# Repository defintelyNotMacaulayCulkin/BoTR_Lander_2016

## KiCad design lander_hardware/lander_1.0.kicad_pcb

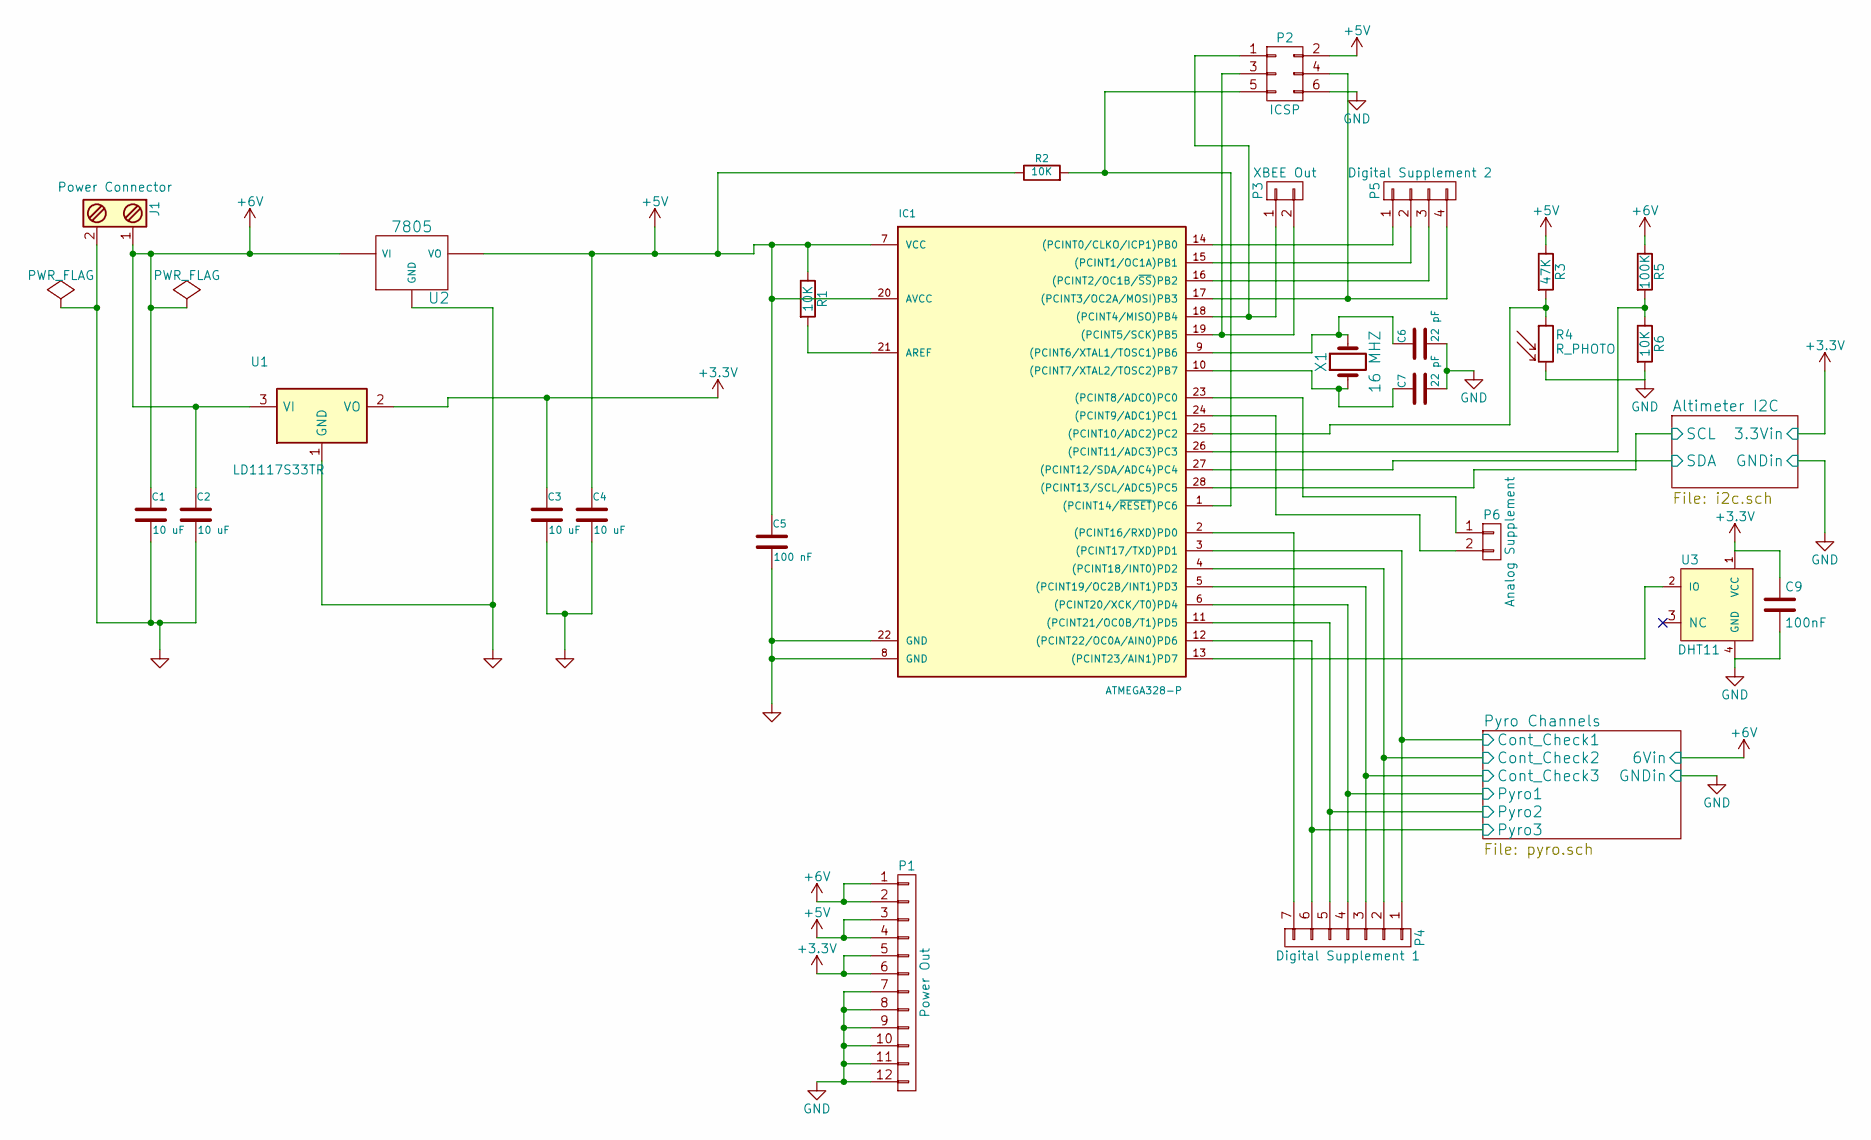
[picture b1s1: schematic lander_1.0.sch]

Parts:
C1, C2, C3, C4: 10 uF; C_Disc_D10.0mm_W2.5mm_P5.00mm
C5: 100 nF; C_Disc_D10.0mm_W2.5mm_P5.00mm
C6, C7: 22 pF; C_Disc_D10.0mm_W2.5mm_P5.00mm
C9: 100nF; C_Disc_D10.0mm_W2.5mm_P5.00mm
IC1: ATMEGA328-P; DIP-28_W7.62mm
J1: Power Connector; bornier2
P1: Power Out; Pin_Header_Straight_1x12_Pitch2.54mm
P2: ICSP; IDC_Header_Straight_6pins
P3: XBEE Out; Pin_Header_Straight_1x02_Pitch2.54mm
P4: Digital Supplement 1; Pin_Header_Straight_1x07_Pitch2.54mm
P5: Digital Supplement 2; Pin_Header_Straight_1x04_Pitch2.54mm
P6: Analog Supplement; Pin_Header_Straight_1x02_Pitch2.54mm
R1, R2, R6: 10K; R_Axial_DIN0207_L6.3mm_D2.5mm_P10.16mm_Horizontal
R3: 47K; R_Axial_DIN0207_L6.3mm_D2.5mm_P10.16mm_Horizontal
R4: R_PHOTO; Resistor_LDR_4.9x4.2_RM2.54
R5: 100K; R_Axial_DIN0207_L6.3mm_D2.5mm_P10.16mm_Horizontal
U1: LD1117S33TR; lm1117_nde
U2: 7805; TO-220
U3: DHT11; dht11
X1: 16 MHZ; Crystal_HC49-U_Vertical

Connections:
+3V3: C3.1, C9.1, P1.5, P1.6, U1.2 (VO), U3.1 (VCC); also elsewhere on the board
+5V: C4.1, C5.1, IC1.7 (VCC), IC1.20 (AVCC), P1.3, P1.4, P2.2, R1.1, R2.1, R3.1, U2.3 (VO); also elsewhere on the board
+6V: C1.1, C2.1, J1.1, P1.1, P1.2, R5.1, U1.3 (VI), U2.1 (VI); also elsewhere on the board
/Altimeter I2C/SCL: IC1.28 ((PCINT13/SCL/ADC5)PC5); also elsewhere on the board
/Altimeter I2C/SDA: IC1.27 ((PCINT12/SDA/ADC4)PC4); also elsewhere on the board
/Pyro Channels/Cont_Check1: IC1.3 ((PCINT17/TXD)PD1), P4.1; also elsewhere on the board
/Pyro Channels/Cont_Check2: IC1.4 ((PCINT18/INT0)PD2), P4.2; also elsewhere on the board
/Pyro Channels/Cont_Check3: IC1.5 ((PCINT19/OC2B/INT1)PD3), P4.3; also elsewhere on the board
/Pyro Channels/Pyro1: IC1.6 ((PCINT20/XCK/T0)PD4), P4.4; also elsewhere on the board
/Pyro Channels/Pyro2: IC1.11 ((PCINT21/OC0B/T1)PD5), P4.5; also elsewhere on the board
/Pyro Channels/Pyro3: IC1.12 ((PCINT22/OC0A/AIN0)PD6), P4.6; also elsewhere on the board
GND: C1.2, C2.2, C3.2, C4.2, C5.2, C6.2, C7.2, C9.2, IC1.8 (GND), IC1.22 (GND), J1.2, P1.7, P1.8, P1.9, P1.10, P1.11, P1.12, P2.6, R4.2, R6.2, U1.1 (GND), U2.2 (GND), U3.4 (GND); also elsewhere on the board
unnamed: C6.1, IC1.9 ((PCINT6/XTAL1/TOSC1)PB6), X1.2
unnamed: C7.1, IC1.10 ((PCINT7/XTAL2/TOSC2)PB7), X1.1
unnamed: IC1.1 ((PCINT14/~RESET~)PC6), P2.5, R2.2
unnamed: IC1.2 ((PCINT16/RXD)PD0), P4.7
unnamed 16: IC1.13 ((PCINT23/AIN1)PD7), U3.2 (IO); also elsewhere on the board
unnamed: IC1.14 ((PCINT0/CLKO/ICP1)PB0), P5.1
unnamed: IC1.15 ((PCINT1/OC1A)PB1), P5.2
unnamed: IC1.16 ((PCINT2/OC1B/~SS~)PB2), P5.3
unnamed: IC1.17 ((PCINT3/OC2A/MOSI)PB3), P2.4, P5.4
unnamed: IC1.18 ((PCINT4/MISO)PB4), P2.1, P3.1
unnamed: IC1.19 ((PCINT5/SCK)PB5), P2.3, P3.2
unnamed: IC1.21 (AREF), R1.2
unnamed: IC1.23 ((PCINT8/ADC0)PC0), P6.1
unnamed: IC1.24 ((PCINT9/ADC1)PC1), P6.2
unnamed: IC1.25 ((PCINT10/ADC2)PC2), R3.2, R4.1
unnamed: IC1.26 ((PCINT11/ADC3)PC3), R5.2, R6.1

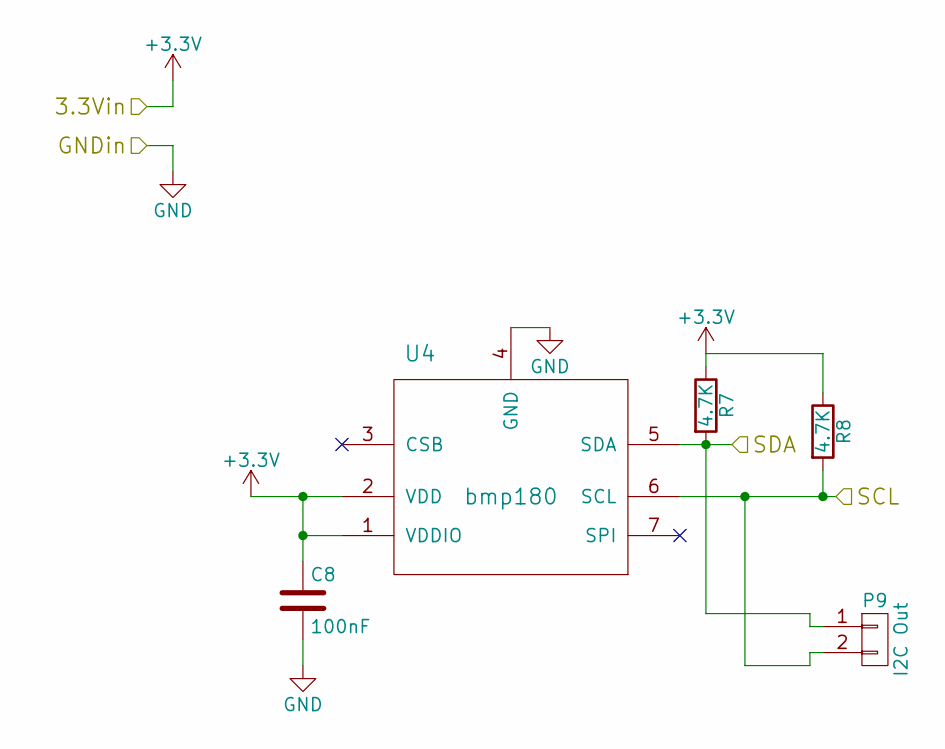
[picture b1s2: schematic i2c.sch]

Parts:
C8: 100nF; C_Disc_D10.0mm_W2.5mm_P5.00mm
P9: I2C Out; Pin_Header_Straight_1x02_Pitch2.54mm
R7, R8: 4.7K; R_Axial_DIN0207_L6.3mm_D2.5mm_P10.16mm_Horizontal
U4: bmp180

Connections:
+3V3: C8.1, R7.1, R8.1, U4.1 (VDDIO), U4.2 (VDD); also elsewhere on the board
/Altimeter I2C/SCL: P9.2, R8.2, U4.6 (SCL); also elsewhere on the board
/Altimeter I2C/SDA: P9.1, R7.2, U4.5 (SDA); also elsewhere on the board
GND: C8.2, U4.4 (GND); also elsewhere on the board

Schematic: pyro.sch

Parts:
J3, J4, J5: Pyro Channel; bornier2
P7: Continuity Jumpers; Pin_Header_Straight_2x03_Pitch2.54mm
P8: Pyro Jumpers; Pin_Header_Straight_2x03_Pitch2.54mm
Q1, Q2, Q3: Q_NPN_BCE; TO-220_Vertical
R9, R11, R13: 1M; R_Axial_DIN0207_L6.3mm_D2.5mm_P10.16mm_Horizontal
R10, R12, R14: 100K; R_Axial_DIN0207_L6.3mm_D2.5mm_P10.16mm_Horizontal

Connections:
+6V: J3.1, J4.1, J5.1; also elsewhere on the board
/Pyro Channels/Cont_Check1: P7.1; also elsewhere on the board
/Pyro Channels/Cont_Check2: P7.3; also elsewhere on the board
/Pyro Channels/Cont_Check3: P7.5; also elsewhere on the board
/Pyro Channels/Pyro1: P8.1; also elsewhere on the board
/Pyro Channels/Pyro2: P8.3; also elsewhere on the board
/Pyro Channels/Pyro3: P8.5; also elsewhere on the board
GND: Q1.3, Q2.3, Q3.3, R9.2, R11.2, R13.2; also elsewhere on the board
unnamed: J3.2, Q1.2, R9.1, R10.1
unnamed: J4.2, Q2.2, R11.1, R12.1
unnamed: J5.2, Q3.2, R13.1, R14.1
unnamed: P7.2, R10.2
unnamed: P7.4, R12.2
unnamed: P7.6, R14.2
unnamed: P8.2, Q1.1
unnamed: P8.4, Q2.1
unnamed: P8.6, Q3.1

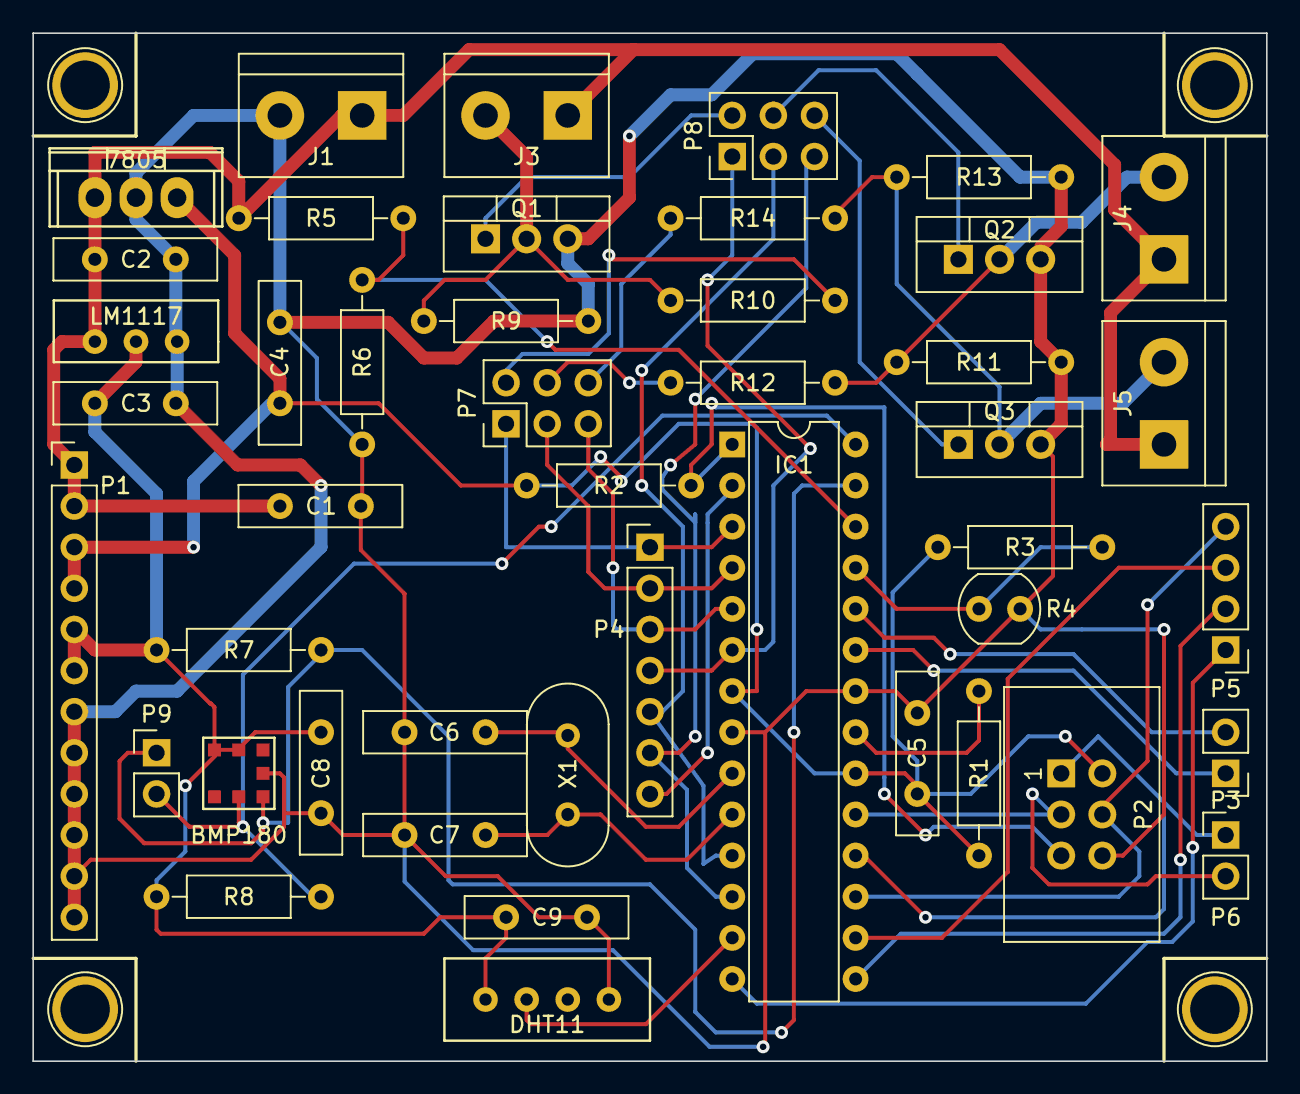
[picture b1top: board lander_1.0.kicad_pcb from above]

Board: 2 copper layers, 76.2 x 63.5 mm, 45 parts (0 on the bottom side), 37 nets.

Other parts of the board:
7805: 7805; TO-220
BMP180: bmp180
DHT11: DHT11; dht11
LM1117: LD1117S33TR; lm1117_nde

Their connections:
+3V3: BMP180.1, BMP180.2, DHT11.1, LM1117.2; also elsewhere on the board
+5V: 7805.3; also elsewhere on the board
+6V: 7805.1, LM1117.3; also elsewhere on the board
/Altimeter I2C/SCL: BMP180.6; also elsewhere on the board
/Altimeter I2C/SDA: BMP180.5; also elsewhere on the board
GND: 7805.2, BMP180.4, DHT11.4, LM1117.1; also elsewhere on the board
unnamed 16: DHT11.2; also elsewhere on the board

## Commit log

2017-01-25 Added test cases for python RDT
2017-01-29 Merged from matthaberbusch/BoTR_Lander_2016
2017-01-29 Added framework for drivers
2017-01-29 More driver framework
2017-02-03 Wrote some basic functions for altimiter & humidity sensors. Check the setup() method though
2017-02-03 Fixed syntax errors in python implementations
2017-02-04 Reorganized example files
2017-02-04 Initial schematic
    This schematic only has the 7805 regulator and the LD1117S33TR regulator so far. I assume the cache is something you need if you don't have the libraries and pcb component files already.
2017-02-05 Fixed more errors with python RDT implementation
2017-02-05 sort of did something
2017-02-05 fixed altitude
2017-02-06 Fixed python RDT implementation
2017-02-06 Fixed checksum bug in C RDT
2017-02-12 fixed DHT I think probably
2017-02-12 made dht global so it actually works
2017-02-12 fixt altimiter and dht drivers
2017-02-17 added code to display graphs and panoramas
2017-02-26 complete rewritten
    code is finally transmitting coordinates correctly, still have to change the format
2017-02-26 Latest lander schematic
2017-02-28 Released first complete schematic
2017-02-28 Added ICSP
2017-02-28 I2C power
2017-03-02 Simplified continuity tester
2017-03-02 Footprints
2017-03-04 Started associating footprints
2017-03-05 Board layout
2017-03-05 Moved some decoupling caps closer
2017-03-05 Updated constraints
2017-03-08 Fixed power transistors being CBE instead of BCE
2017-03-09 Added tracks
    I made some of the ground tracks 0.8 mm as well. What else should be wider?
2017-03-10 Track width, via size, screws
2017-03-10 Added gerber files
2017-03-11 Tracks didnt widen in last commit, fixed
2017-03-15 Started fleshing out the protocol for camera data transmissions
2017-03-15 Accidentally forgot a file last commit
2017-03-15 Added skeletons for more drivers
2017-03-15 Arduino doesn't support 8 byte doubles, changing telemetry header for cross platform compatibility
2017-03-17 thingy for latch opener servo
2017-03-19 added pryrochannel setup and output
2017-03-19 continuity thingy
